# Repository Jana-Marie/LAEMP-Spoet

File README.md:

# LÄMP-Spöt

LÄMP-Spöt is an open source, multi-channel (multi-colour) LED spot that aims to deliver high quality effect-lighting through up to 6 LED-channels with ~10W each. This allows for a broader colour range than just RGB or RGBW, but RGB + non-mixed secondaries (i.e. RGB, Yellow, Cyan, Purple), RGB + Yellow + Whites, a variety of White tones (with degrees of Red, Blue and Green hues) and of course effect channels (i.e. UV, IR). In that, I have assembled various spöts that follow these suggestions, one that features RGBY + UV + IR, RGBY + IR + White and one with three channels of white + UV + IR for plants

<table>
	<tbody>
		<tr>
			<td>
				
			</td>
			<td>
				
			</td>
		</tr>
	</tbody>
</table>

Each spöt consists of at least an LED carrier and a driver board. The driver-board is fairly generic, but can be optimized for each LED board by conforming the DCDC-Shunts to match the maximum LED current of that channel. You can of course set all channels to max current in hardware and use software-limiting. The LED carrier boards are a bit more specific due to their LED footprints. In addition you will probably want to sink the LEDs heat to somewhere, I've chosen "LA ICK 17x17" heatsinks from fisherelektronik.

You can find a [video of a preliminary board in action here.](https://chaos.social/@janamarie/110854704275031346)

It's not neccesarrily fixed on a single LED series by virtue of the LED-carrier being interchangable. I focused myself on using the Luxeon C series, it featurs a high variety of colours in the same package, as well as various binned whites. There is also a breakout board for a 6-Channel (RGBY, W, UV), single package led, available through chinese companies.

<a href="https://otmm.lumileds.com/adaptivemedia/f5fbe66cb9d857d62d895f92b8d6be3cc5919925">
	<table>
		<tbody>
			<tr>
				<td colspan="6">
					Available Lumileds Luxeon C Color Series measured and published by Lumileds (click me to assess the source)
				</td>
			</tr>
			<tr>
				<td colspan="3">
					
				</td>
				<td colspan="3">
					
				</td>
			</tr>
			<tr>
				<td colspan="6">
					Available Lumileds Luxeon C White Series measured and published by Lumileds (click me to assess the source)
				</td>
			</tr>
			<tr>
				<td colspan="2">
					
				</td>
				<td colspan="2">
					
				</td>
				<td colspan="2">
					
				</td>
			</tr>
		</tbody>
	</table>
</a>

The driver-board hosts an STM32G431 with a huge surplus in computing power, allowing for generous colour-space conversions and color-to-wavelength matching. None of this is implemented as of right now (~09-2024). It requires a 15-20V USB-PD source to run. The MCU speaks USB FS through the Type-C receptacle as well. A 2mm pinheader with power, signals and I2C allows for connectivity through shield-like addons (blame me for only having USB FS as on-board connectivity :/). Each channel features a TPS54201 CC Buck as analog-current-source allowing each channel to run at up to 1.5A @ 20V.

**Please do not reproduce this project if you are not willing to put some work and money into your reproduction, it's mechanical setup is highly alpha and there is little firmware.**

<table>
	<tbody>
		<tr>
			<td>
				
			</td>
			<td>
				
			</td>
		</tr>
	</tbody>
</table>

---

## Schematics

<a href="https://github.com/Jana-Marie/LAEMP-Spoet/tree/main/led-driver/schematic.pdf">
	<table>
		<tbody>
			<tr>
				<td colspan="2">
					Link to PDF
				</td>
			</tr>
			<tr>
				<td>
					
				</td>
				<td>
					
				</td>
			</tr>
		</tbody>
	</table>
</a>

---

## Todos

 - [ ] Add a connectivity shield that allows for control via either DMX, Artnet or Other
 - [ ] Design a rigid case that features proper input jacks, a ¼ inch screw mount and proper cooling

### Bugs & PCB-enhancements

 - [ ] Improve cooling options
   - [ ] Connect the fan output to a PWM or enable
   - [ ] Add a temperature-probe for the fan

---

## License

Copyright Jana Marie Hemsing 2023.

This source describes Open Hardware and is licensed under the CERN-OHL-S v2.

You may redistribute and modify this source and make products using it under
the terms of the CERN-OHL-S v2 (https://ohwr.org/cern_ohl_s_v2.txt).

This source is distributed WITHOUT ANY EXPRESS OR IMPLIED WARRANTY,
INCLUDING OF MERCHANTABILITY, SATISFACTORY QUALITY AND FITNESS FOR A
PARTICULAR PURPOSE. Please see the CERN-OHL-S v2 for applicable conditions.

Source location: https://github.com/Jana-Marie/LAEMP-Spoet

As per CERN-OHL-S v2 section 4, should You produce hardware based on this
source, You must where practicable maintain the Source Location visible
on the external case of the Gizmo or other products you make using this
source.

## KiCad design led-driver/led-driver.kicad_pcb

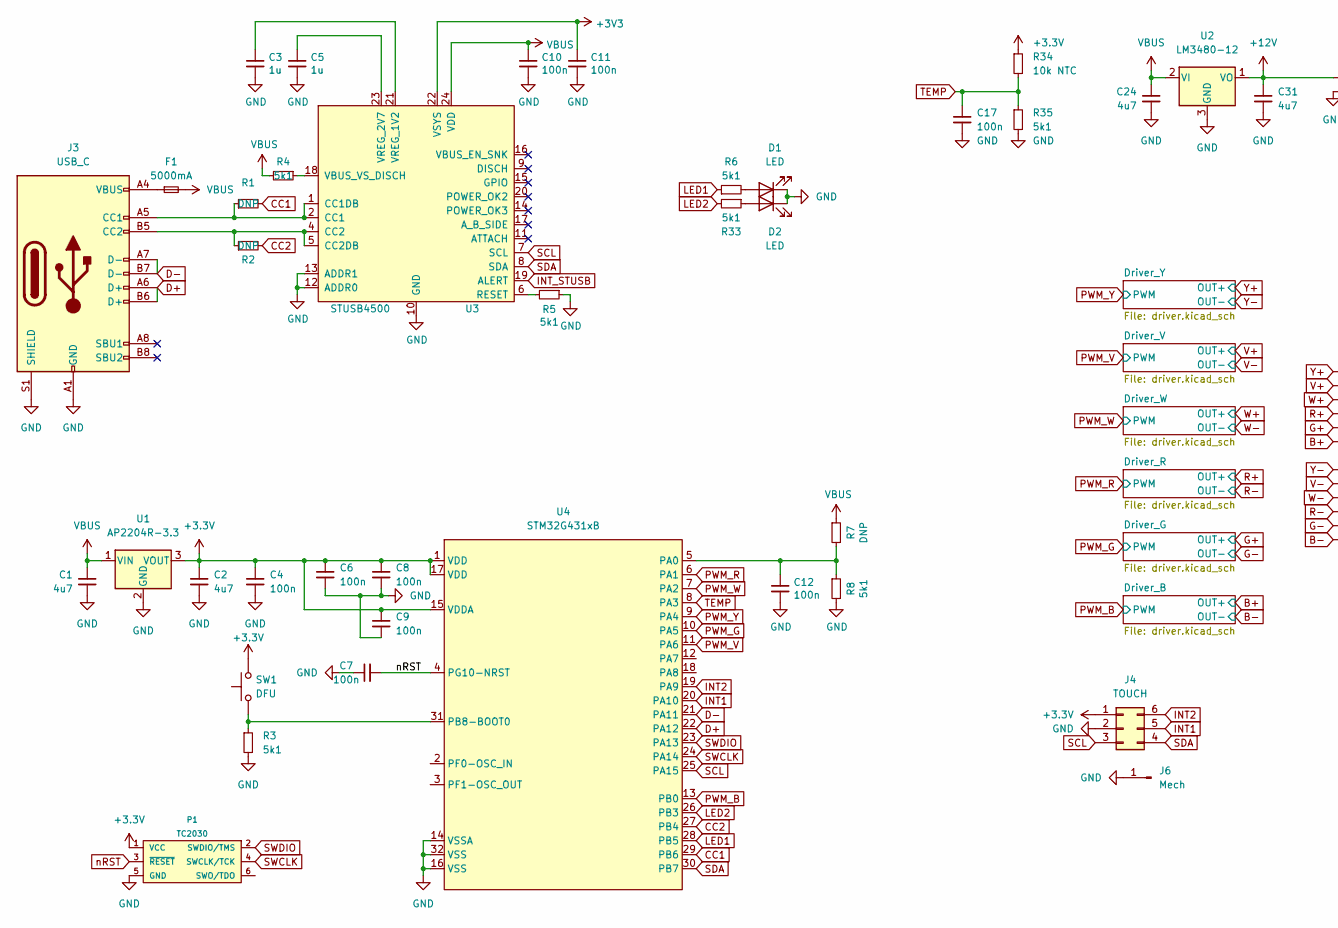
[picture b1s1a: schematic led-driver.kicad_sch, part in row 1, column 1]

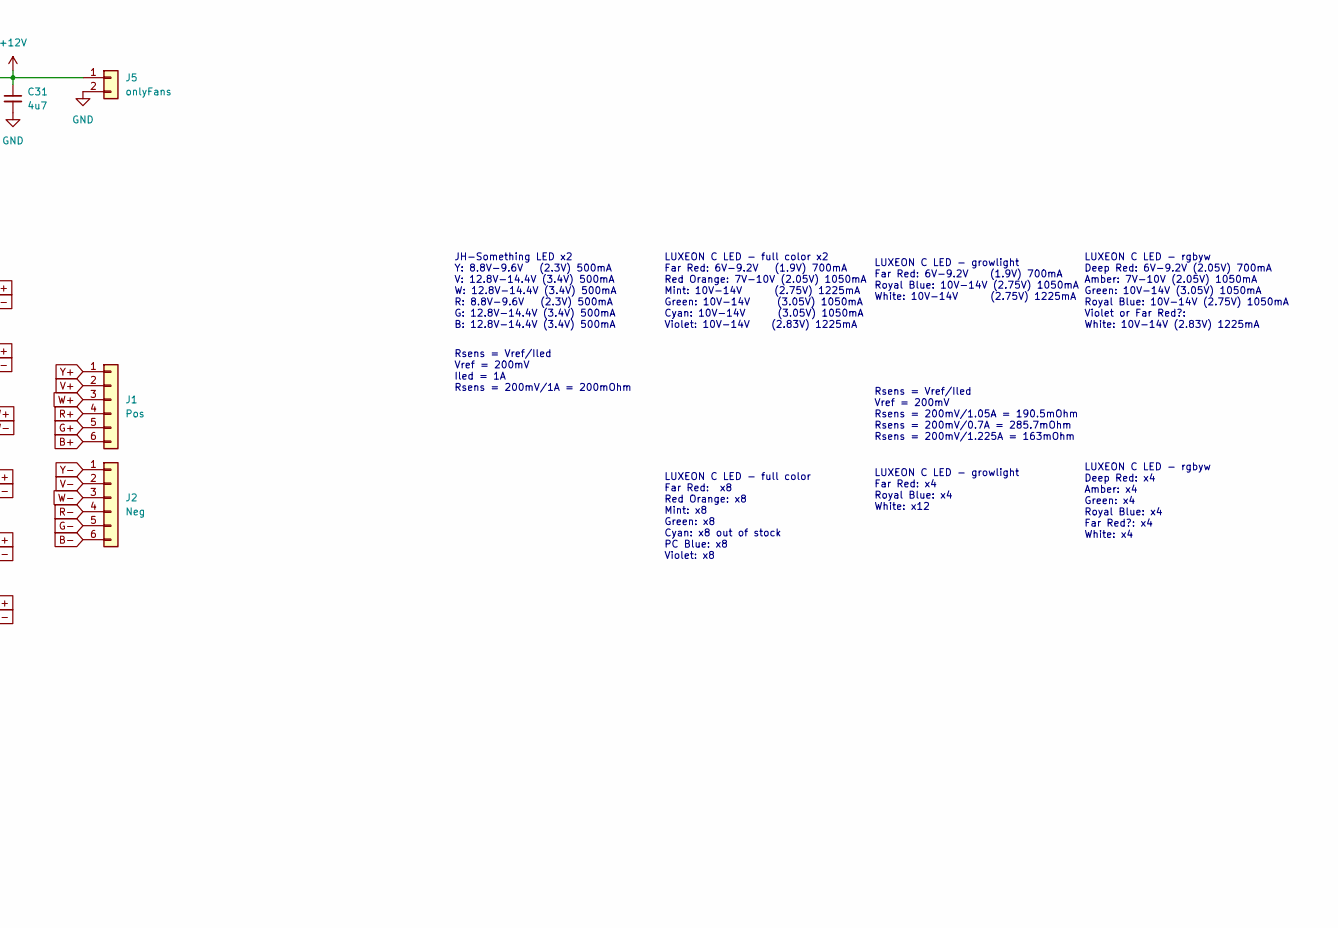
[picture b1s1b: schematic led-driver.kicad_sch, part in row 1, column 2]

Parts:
C1, C2, C24, C31: 4u7; C_0603
C3, C5: 1u; C_0402
C4, C6, C7, C8, C9, C10, C11, C12, C17: 100n; C_0402
D1, D2: LED; LED_0603_1608Metric
F1: 5000mA; R_1210_3225Metric
J1: Pos; PinSocket_1x06_P2.00mm_Vertical_center
J2: Neg; PinSocket_1x06_P2.00mm_Vertical_center
J3: USB_C; USB-C 16Pin
J4: TOUCH; PinSocket_1x06_P2.00mm_Vertical_center
J5: onlyFans; PinHeader_1x02_P2.00mm_Vertical
J6: Mech; PinHeader_1x01_P2.00mm_Vertical
P1: TC2030
R1, R2, R7: DNP; R_0402
R3, R4, R5, R6, R8, R33, R35: 5k1; R_0402
R34: 10k NTC; R_0402
SW1: DFU; SW_SPST_PTS810
U1: AP2204R-3.3; SOT-89-3
U2: LM3480-12; SOT-23
U3: STUSB4500; QFN-24-1EP_4x4mm_P0.5mm_EP2.7x2.7mm
U4: STM32G431xB; LQFP-32_7x7mm_P0.8mm

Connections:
+12V: C31.1, J5.1, U2.1 (VO)
B+: J1.6; also elsewhere on the board
B-: J2.6; also elsewhere on the board
CC1: R1.2, U4.29 (PB6)
CC2: R2.2, U4.27 (PB4)
D+: J3.A6 (D+), J3.B6 (D+), U4.22 (PA12)
D-: J3.A7 (D-), J3.B7 (D-), U4.21 (PA11)
G+: J1.5; also elsewhere on the board
G-: J2.5; also elsewhere on the board
GND: C1.2, C2.2, C3.2, C4.2, C5.2, C6.2, C7.1, C8.2, C9.2, C10.2, C11.2, C12.2, C17.2, C24.2, C31.2, D1.1 (K), D2.1 (K), J3.A1 (GND), J3.A12 (GND), J3.B1 (GND), J3.B12 (GND), J3.S1 (SHIELD), J4.2, J5.2, J6.1, P1.5 (GND), R3.2, R5.1, R8.2, R35.2, U1.2 (GND), U2.3 (GND), U3.10 (GND), U3.12 (ADDR0), U3.13 (ADDR1), U3.25 (GND), U4.14 (VSSA), U4.16 (VSS), U4.32 (VSS); also elsewhere on the board
INT1: J4.5, U4.20 (PA10)
INT2: J4.6, U4.19 (PA9)
INT_STUSB: U3.19 (ALERT)
LED1: R6.1, U4.28 (PB5)
LED2: R33.2, U4.26 (PB3)
unnamed: D1.2 (A), R6.2
unnamed: D2.2 (A), R33.1
unnamed: F1.1, J3.A4 (VBUS), J3.A9 (VBUS), J3.B4 (VBUS), J3.B9 (VBUS)
unnamed: J3.A5 (CC1), R1.1, U3.1 (CC1DB), U3.2 (CC1)
unnamed: J3.B5 (CC2), R2.1, U3.4 (CC2), U3.5 (CC2DB)
unnamed: R5.2, U3.6 (RESET)
unnamed: R4.1, U3.18 (VBUS_VS_DISCH)
unnamed: C3.1, U3.21 (VREG_1V2)
unnamed: C5.1, U3.23 (VREG_2V7)
unnamed: C12.1, R7.2, R8.1, U4.5 (PA0)
unnamed: R3.1, SW1.1, U4.31 (PB8-BOOT0)
PWM_B: U4.13 (PB0); also elsewhere on the board
PWM_G: U4.10 (PA5); also elsewhere on the board
PWM_R: U4.6 (PA1); also elsewhere on the board
PWM_V: U4.11 (PA6); also elsewhere on the board
PWM_W: U4.7 (PA2); also elsewhere on the board
PWM_Y: U4.9 (PA4); also elsewhere on the board
R+: J1.4; also elsewhere on the board
R-: J2.4; also elsewhere on the board
SCL: J4.3, U3.7 (SCL), U4.25 (PA15)
SDA: J4.4, U3.8 (SDA), U4.30 (PB7)
SWCLK: P1.4 (SWCLK/TCK), U4.24 (PA14)
SWDIO: P1.2 (SWDIO/TMS), U4.23 (PA13)
TEMP: C17.1, R34.2, R35.1, U4.8 (PA3)
V+: J1.2; also elsewhere on the board
V-: J2.2; also elsewhere on the board
VBUS: C1.1, C10.1, C24.1, F1.2, R4.2, R7.1, U1.1 (VIN), U2.2 (VI), U3.24 (VDD); also elsewhere on the board
W+: J1.3; also elsewhere on the board
W-: J2.3; also elsewhere on the board
Y+: J1.1; also elsewhere on the board
Y-: J2.1; also elsewhere on the board
nRST: C7.2, P1.3 (~RESET), U4.4 (PG10-NRST)

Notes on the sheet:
Rsens = Vref/Iled Vref = 200mV Iled = 1A Rsens = 200mV/1A = 200mOhm
LUXEON C LED - rgbyw Deep Red: 6V-9.2V (2.05V) 700mA Amber: 7V-10V (2.05V) 1050mA Green: 10V-14V (3.05V) 1050mA Royal Blue: 10V-14V (2.75V) 1050mA Violet or Far Red?: White: 10V-14V (2.83V) 1225mA
LUXEON C LED - growlight Far Red: x4 Royal Blue: x4 White: x12
LUXEON C LED - rgbyw Deep Red: x4 Amber: x4 Green: x4 Royal Blue: x4 Far Red?: x4 White: x4
Rsens = Vref/Iled Vref = 200mV Rsens = 200mV/1.05A = 190.5mOhm Rsens = 200mV/0.7A = 285.7mOhm Rsens = 200mV/1.225A = 163mOhm
LUXEON C LED - full color Far Red: x8 Red Orange: x8 Mint: x8 Green: x8 Cyan: x8 out of stock PC Blue: x8 Violet: x8
LUXEON C LED - growlight Far Red: 6V-9.2V (1.9V) 700mA Royal Blue: 10V-14V (2.75V) 1050mA White: 10V-14V (2.75V) 1225mA
JH-Something LED x2 Y: 8.8V-9.6V (2.3V) 500mA V: 12.8V-14.4V (3.4V) 500mA W: 12.8V-14.4V (3.4V) 500mA R: 8.8V-9.6V (2.3V) 500mA G: 12.8V-14.4V (3.4V) 500mA B: 12.8V-14.4V (3.4V) 500mA
LUXEON C LED - full color x2 Far Red: 6V-9.2V (1.9V) 700mA Red Orange: 7V-10V (2.05V) 1050mA Mint: 10V-14V (2.75V) 1225mA Green: 10V-14V (3.05V) 1050mA Cyan: 10V-14V (3.05V) 1050mA Violet: 10V-14V (2.83V) 1225mA

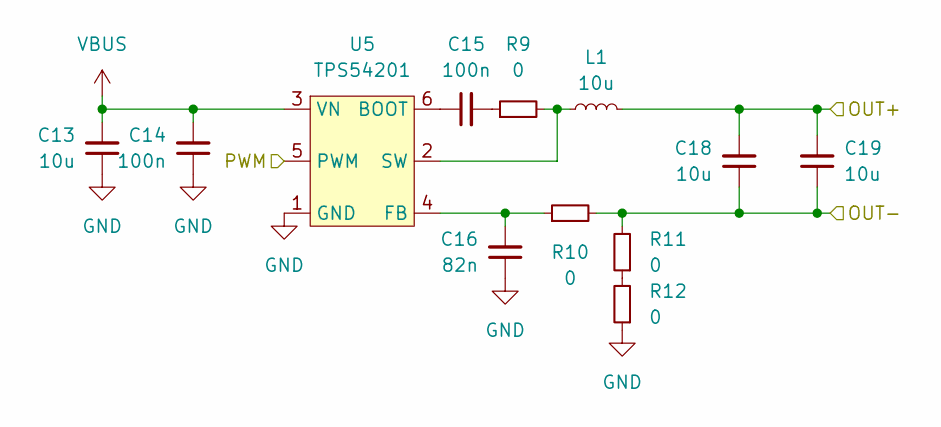
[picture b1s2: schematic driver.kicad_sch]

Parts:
C13, C18, C19: 10u; C_0805
C14, C15: 100n; C_0603
C16: 82n; C_0402
L1: 10u; L_Taiyo-Yuden_MD-4040
R9: 0; R_0603
R10: 0; R_0402
R11, R12: 0; R_0805
U5: TPS54201; SOT-23-6

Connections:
GND: C13.1, C14.1, C16.1, R12.1, U5.1 (GND); also elsewhere on the board
unnamed: C15.2, R9.1
unnamed: R11.1, R12.2
unnamed: C15.1, U5.6 (BOOT)
unnamed: C16.2, R10.1, U5.4 (FB)
unnamed: L1.1, R9.2, U5.2 (SW)
PWM_Y: U5.5 (PWM); also elsewhere on the board
VBUS: C13.2, C14.2, U5.3 (VN); also elsewhere on the board
Y+: C18.2, C19.2, L1.2; also elsewhere on the board
Y-: C18.1, C19.1, R10.2, R11.2; also elsewhere on the board

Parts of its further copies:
C20, C25, C26, C27, C32, C33, C34, C39, C40, C41, C46, C47, C48, C53, C54: 10u; C_0805
C21, C22, C28, C29, C35, C36, C42, C43, C49, C50: 100n; C_0603
C23, C30, C37, C44, C51: 82n; C_0402
L2, L3, L4, L5, L6: 10u; L_Taiyo-Yuden_MD-4040
R13, R17, R21, R25, R29: 0; R_0603
R14, R18, R22, R26, R30: 0; R_0402
R15, R16, R19, R20, R23, R24, R27, R28, R31, R32: 0; R_0805
U6, U7, U8, U9, U10: TPS54201; SOT-23-6

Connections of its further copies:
B+: C53.2, C54.2, L6.2; also elsewhere on the board
B-: C53.1, C54.1, R30.2, R31.2; also elsewhere on the board
G+: C46.2, C47.2, L5.2; also elsewhere on the board
G-: C46.1, C47.1, R26.2, R27.2; also elsewhere on the board
GND: C20.1, C21.1, C23.1, C27.1, C28.1, C30.1, C34.1, C35.1, C37.1, C41.1, C42.1, C44.1, C48.1, C49.1, C51.1, R16.1, R20.1, R24.1, R28.1, R32.1, U6.1 (GND), U7.1 (GND), U8.1 (GND), U9.1 (GND), U10.1 (GND); also elsewhere on the board
unnamed: C22.2, R13.1
unnamed: C29.2, R17.1
unnamed: C36.2, R21.1
unnamed: C43.2, R25.1
unnamed: C50.2, R29.1
unnamed: R15.1, R16.2
unnamed: R19.1, R20.2
unnamed: R23.1, R24.2
unnamed: R27.1, R28.2
unnamed: R31.1, R32.2
unnamed: C22.1, U6.6 (BOOT)
unnamed: C23.2, R14.1, U6.4 (FB)
unnamed: L2.1, R13.2, U6.2 (SW)
unnamed: C29.1, U7.6 (BOOT)
unnamed: C30.2, R18.1, U7.4 (FB)
unnamed: L3.1, R17.2, U7.2 (SW)
unnamed: C36.1, U8.6 (BOOT)
unnamed: C37.2, R22.1, U8.4 (FB)
unnamed: L4.1, R21.2, U8.2 (SW)
unnamed: C43.1, U9.6 (BOOT)
unnamed: C44.2, R26.1, U9.4 (FB)
unnamed: L5.1, R25.2, U9.2 (SW)
unnamed: C50.1, U10.6 (BOOT)
unnamed: C51.2, R30.1, U10.4 (FB)
unnamed: L6.1, R29.2, U10.2 (SW)
PWM_B: U10.5 (PWM); also elsewhere on the board
PWM_G: U9.5 (PWM); also elsewhere on the board
PWM_R: U8.5 (PWM); also elsewhere on the board
PWM_V: U6.5 (PWM); also elsewhere on the board
PWM_W: U7.5 (PWM); also elsewhere on the board
R+: C39.2, C40.2, L4.2; also elsewhere on the board
R-: C39.1, C40.1, R22.2, R23.2; also elsewhere on the board
V+: C25.2, C26.2, L2.2; also elsewhere on the board
V-: C25.1, C26.1, R14.2, R15.2; also elsewhere on the board
VBUS: C20.2, C21.2, C27.2, C28.2, C34.2, C35.2, C41.2, C42.2, C48.2, C49.2, U6.3 (VN), U7.3 (VN), U8.3 (VN), U9.3 (VN), U10.3 (VN); also elsewhere on the board
W+: C32.2, C33.2, L3.2; also elsewhere on the board
W-: C32.1, C33.1, R18.2, R19.2; also elsewhere on the board

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
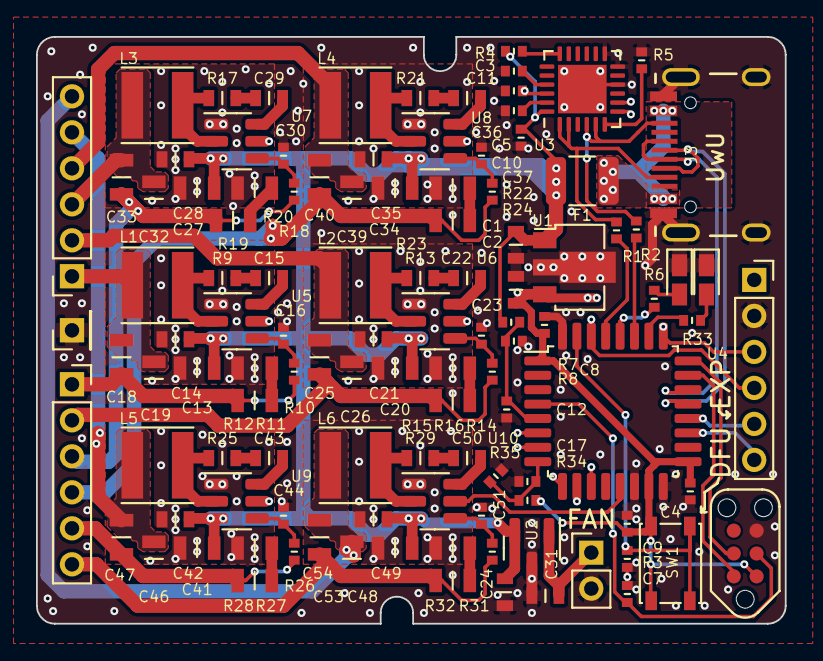
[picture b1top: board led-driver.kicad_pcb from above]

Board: 4 copper layers, 41.6 x 32.6 mm, 112 parts (0 on the bottom side), 77 nets.

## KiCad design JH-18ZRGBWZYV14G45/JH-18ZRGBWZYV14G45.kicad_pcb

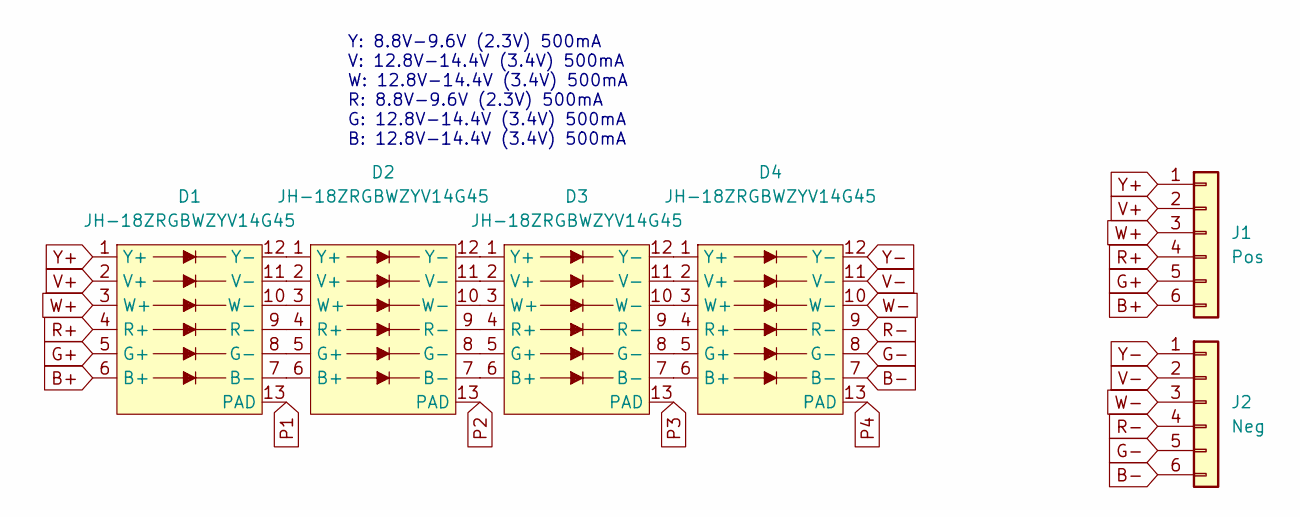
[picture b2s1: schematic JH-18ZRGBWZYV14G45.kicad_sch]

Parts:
D1, D2, D3, D4: JH-18ZRGBWZYV14G45
J1: Pos; CONN_1x06_SMD_SIDE
J2: Neg; CONN_1x06_SMD_SIDE

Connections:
B+: D1.6 (B+), J1.6
B-: D4.7 (B-), J2.6
G+: D1.5 (G+), J1.5
G-: D4.8 (G-), J2.5
unnamed: D1.7 (B-), D2.6 (B+)
unnamed: D1.8 (G-), D2.5 (G+)
unnamed: D1.9 (R-), D2.4 (R+)
unnamed: D1.10 (W-), D2.3 (W+)
unnamed: D1.11 (V-), D2.2 (V+)
unnamed: D1.12 (Y-), D2.1 (Y+)
unnamed: D2.7 (B-), D3.6 (B+)
unnamed: D2.8 (G-), D3.5 (G+)
unnamed: D2.9 (R-), D3.4 (R+)
unnamed: D2.10 (W-), D3.3 (W+)
unnamed: D2.11 (V-), D3.2 (V+)
unnamed: D2.12 (Y-), D3.1 (Y+)
unnamed: D3.7 (B-), D4.6 (B+)
unnamed: D3.8 (G-), D4.5 (G+)
unnamed: D3.9 (R-), D4.4 (R+)
unnamed: D3.10 (W-), D4.3 (W+)
unnamed: D3.11 (V-), D4.2 (V+)
unnamed: D3.12 (Y-), D4.1 (Y+)
P1: D1.13 (PAD)
P2: D2.13 (PAD)
P3: D3.13 (PAD)
P4: D4.13 (PAD)
R+: D1.4 (R+), J1.4
R-: D4.9 (R-), J2.4
V+: D1.2 (V+), J1.2
V-: D4.11 (V-), J2.2
W+: D1.3 (W+), J1.3
W-: D4.10 (W-), J2.3
Y+: D1.1 (Y+), J1.1
Y-: D4.12 (Y-), J2.1

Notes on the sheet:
Y: 8.8V-9.6V (2.3V) 500mA V: 12.8V-14.4V (3.4V) 500mA W: 12.8V-14.4V (3.4V) 500mA R: 8.8V-9.6V (2.3V) 500mA G: 12.8V-14.4V (3.4V) 500mA B: 12.8V-14.4V (3.4V) 500mA

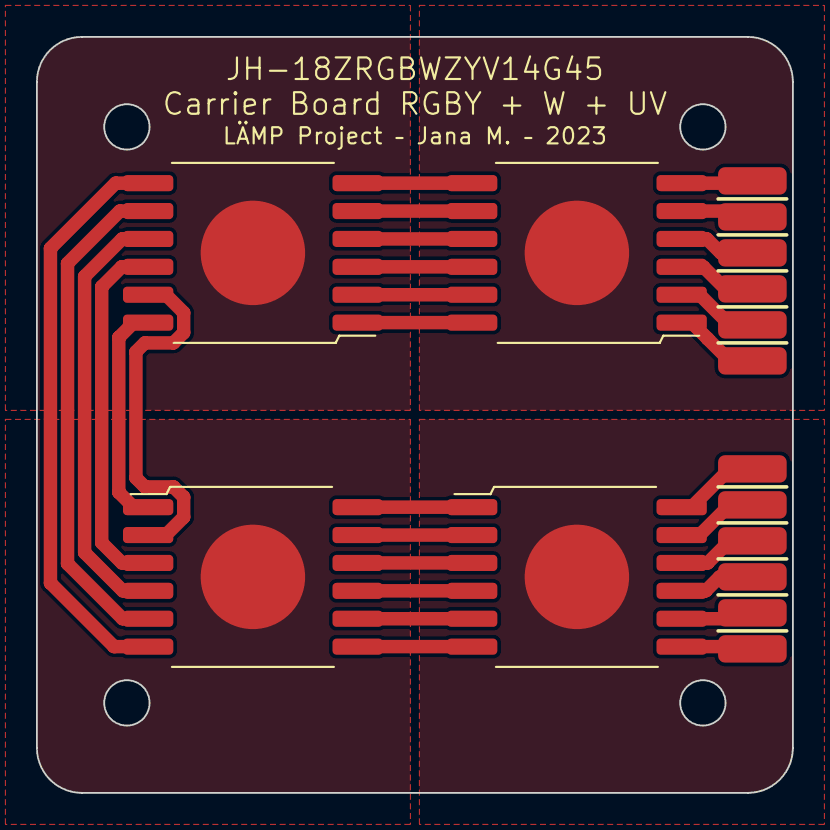
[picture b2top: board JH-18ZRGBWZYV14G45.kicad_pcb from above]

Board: 2 copper layers, 42.0 x 42.0 mm, 6 parts (0 on the bottom side), 30 nets.

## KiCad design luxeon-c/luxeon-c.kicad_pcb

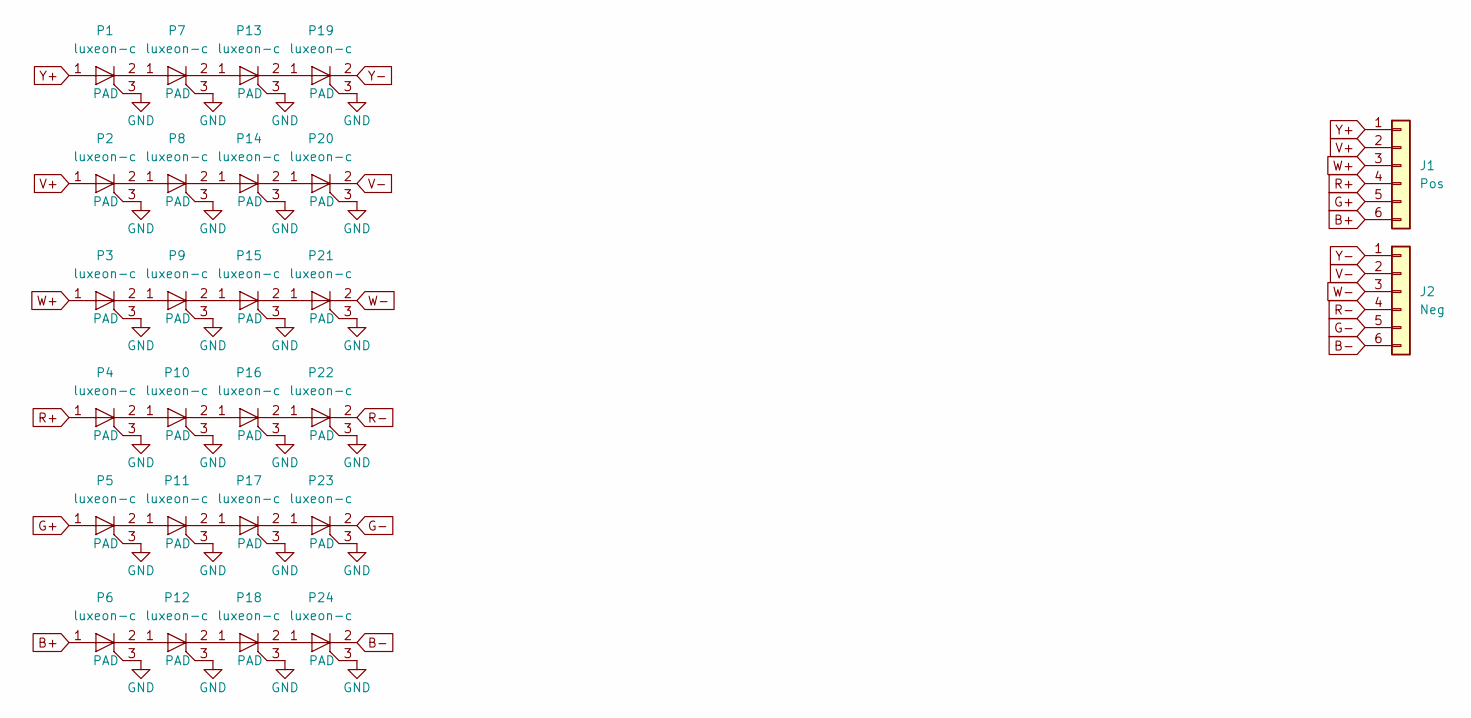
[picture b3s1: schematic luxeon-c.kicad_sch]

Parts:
J1: Pos; CONN_1x06_SMD_SIDE
J2: Neg; CONN_1x06_SMD_SIDE
P1, P2, P3, P4, P5, P6, P7, P8, P9, P10, P11, P12, P13, P14, P15, P16, P17, P18, P19, P20, P21, P22, P23, P24: luxeon-c

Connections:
B+: J1.6, P6.1
B-: J2.6, P24.2
G+: J1.5, P5.1
G-: J2.5, P23.2
GND: P1.3 (PAD), P2.3 (PAD), P3.3 (PAD), P4.3 (PAD), P5.3 (PAD), P6.3 (PAD), P7.3 (PAD), P8.3 (PAD), P9.3 (PAD), P10.3 (PAD), P11.3 (PAD), P12.3 (PAD), P13.3 (PAD), P14.3 (PAD), P15.3 (PAD), P16.3 (PAD), P17.3 (PAD), P18.3 (PAD), P19.3 (PAD), P20.3 (PAD), P21.3 (PAD), P22.3 (PAD), P23.3 (PAD), P24.3 (PAD)
unnamed: P1.2, P7.1
unnamed: P2.2, P8.1
unnamed: P3.2, P9.1
unnamed: P4.2, P10.1
unnamed: P10.2, P16.1
unnamed: P5.2, P11.1
unnamed: P11.2, P17.1
unnamed: P6.2, P12.1
unnamed: P12.2, P18.1
unnamed: P7.2, P13.1
unnamed: P13.2, P19.1
unnamed: P8.2, P14.1
unnamed: P14.2, P20.1
unnamed: P9.2, P15.1
unnamed: P15.2, P21.1
unnamed: P16.2, P22.1
unnamed: P17.2, P23.1
unnamed: P18.2, P24.1
R+: J1.4, P4.1
R-: J2.4, P22.2
V+: J1.2, P2.1
V-: J2.2, P20.2
W+: J1.3, P3.1
W-: J2.3, P21.2
Y+: J1.1, P1.1
Y-: J2.1, P19.2

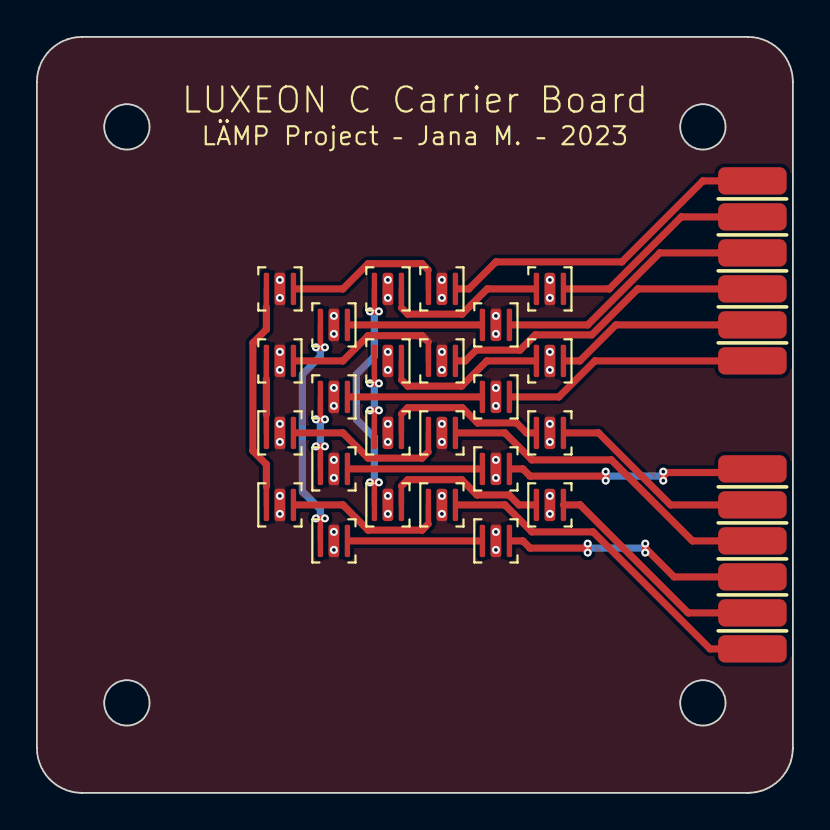
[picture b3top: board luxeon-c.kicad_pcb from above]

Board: 2 copper layers, 42.0 x 42.0 mm, 26 parts (0 on the bottom side), 31 nets.

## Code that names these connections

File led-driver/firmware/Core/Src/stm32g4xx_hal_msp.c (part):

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
    __HAL_RCC_GPIOA_CLK_ENABLE();
    /**ADC1 GPIO Configuration
    PA0     ------> ADC1_IN1
    PA3     ------> ADC1_IN4
    */
    GPIO_InitStruct.Pin = GPIO_PIN_0|GPIO_PIN_3;
    GPIO_InitStruct.Mode = GPIO_MODE_ANALOG;
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    __HAL_RCC_ADC12_CLK_DISABLE();

    /**ADC1 GPIO Configuration
    PA0     ------> ADC1_IN1
    PA3     ------> ADC1_IN4
    */
    HAL_GPIO_DeInit(GPIOA, GPIO_PIN_0|GPIO_PIN_3);

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    __HAL_RCC_GPIOA_CLK_ENABLE();
    __HAL_RCC_GPIOB_CLK_ENABLE();
    /**I2C1 GPIO Configuration
    PA15     ------> I2C1_SCL
    PB7     ------> I2C1_SDA
    */
    GPIO_InitStruct.Pin = GPIO_PIN_15;
    GPIO_InitStruct.Mode = GPIO_MODE_AF_OD;
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    __HAL_RCC_I2C1_CLK_DISABLE();

    /**I2C1 GPIO Configuration
    PA15     ------> I2C1_SCL
    PB7     ------> I2C1_SDA
    */
    HAL_GPIO_DeInit(GPIOA, GPIO_PIN_15);

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  /* USER CODE END TIM2_MspPostInit 0 */
    __HAL_RCC_GPIOA_CLK_ENABLE();
    /**TIM2 GPIO Configuration
    PA1     ------> TIM2_CH2
    PA2     ------> TIM2_CH3
    PA5     ------> TIM2_CH1
    */
    GPIO_InitStruct.Pin = GPIO_PIN_1|GPIO_PIN_2|GPIO_PIN_5;
    GPIO_InitStruct.Mode = GPIO_MODE_AF_PP;
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    __HAL_RCC_GPIOA_CLK_ENABLE();
    __HAL_RCC_GPIOB_CLK_ENABLE();
    /**TIM3 GPIO Configuration
    PA4     ------> TIM3_CH2
    PA6     ------> TIM3_CH1
    PB0     ------> TIM3_CH3
    */
    GPIO_InitStruct.Pin = GPIO_PIN_4|GPIO_PIN_6;
    GPIO_InitStruct.Mode = GPIO_MODE_AF_PP;
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
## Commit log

2023-08-08 added gitignore
2023-08-08 added fw
2023-08-08 added led driver
2023-08-08 added luxeon-c board
2023-08-08 added JH board
2023-08-08 added LZ7 board, untested!
2024-09-14 added images
2024-09-14 added CERN OHL-S v2.0 license
2024-09-14 added schematic files
2024-09-14 fixed typos in readme
2024-09-14 added link to pdf

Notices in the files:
led-driver/firmware/Core/Src/stm32g4xx_hal_msp.c:
Copyright (c) 2023 STMicroelectronics.
All rights reserved.
This software is licensed under terms that can be found in the LICENSE file
